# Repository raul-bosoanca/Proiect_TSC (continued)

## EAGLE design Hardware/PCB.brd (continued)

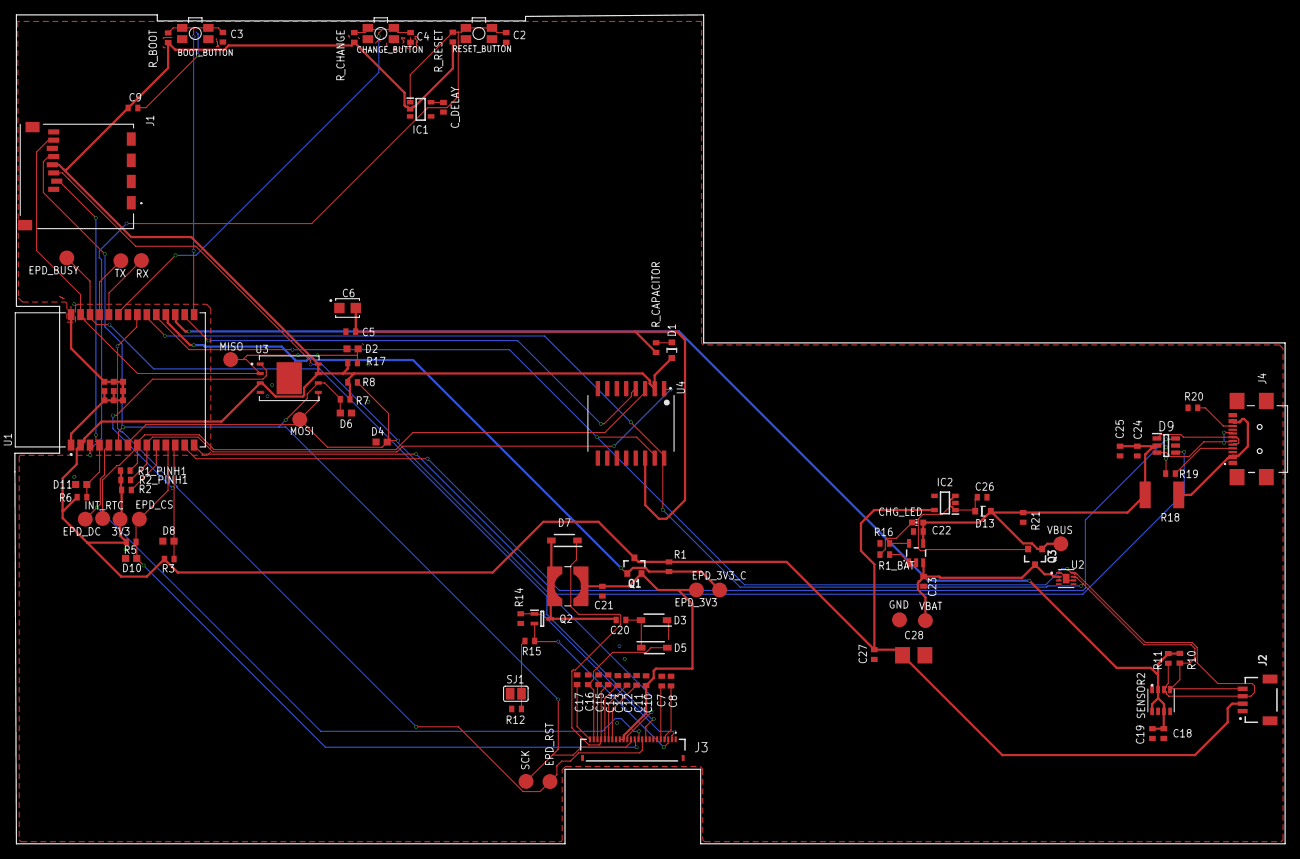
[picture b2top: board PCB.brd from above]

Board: 2 copper layers, 170.4 x 111.2 mm, 102 parts (0 on the bottom side), 55 nets.

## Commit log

2025-04-06 Added sch and brd files
2025-04-06 Changed thickness of PCB, ground plane visible
2025-04-06 Added manufacturing files
2025-04-06 Create LICENSE
2025-04-06 Add top view of the pcv
2025-04-06 Added board as 3d step
2025-04-06 Added images of whole project
2025-04-06 Add step f3z files of final product
2025-04-06 Add BOM with buy links and datasheet
2025-04-06 added BOM as csv
2025-04-10 Update README.md to add BOM table
2025-04-10 update capacitor value
2025-04-14 Solved bugs of routes, GND pour and silkscreen
2025-04-14 Add files via upload
    Solved bugs on routes, GND pour and silkscreen
2025-04-15 Solved wrong routes, added ground plane, fixed silkscreen
